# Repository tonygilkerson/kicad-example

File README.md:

# kicad-example

In most cases, my KiCad projects live in a subdirectory named `kicad` within a larger project.

> **Example**: ~/github/tonygilkerson/esphome-projects/garage-door-side-entrance/kicad

This project contains a very simple KiCad project named `hiki` to illiterate how I structure KiCad projects.x

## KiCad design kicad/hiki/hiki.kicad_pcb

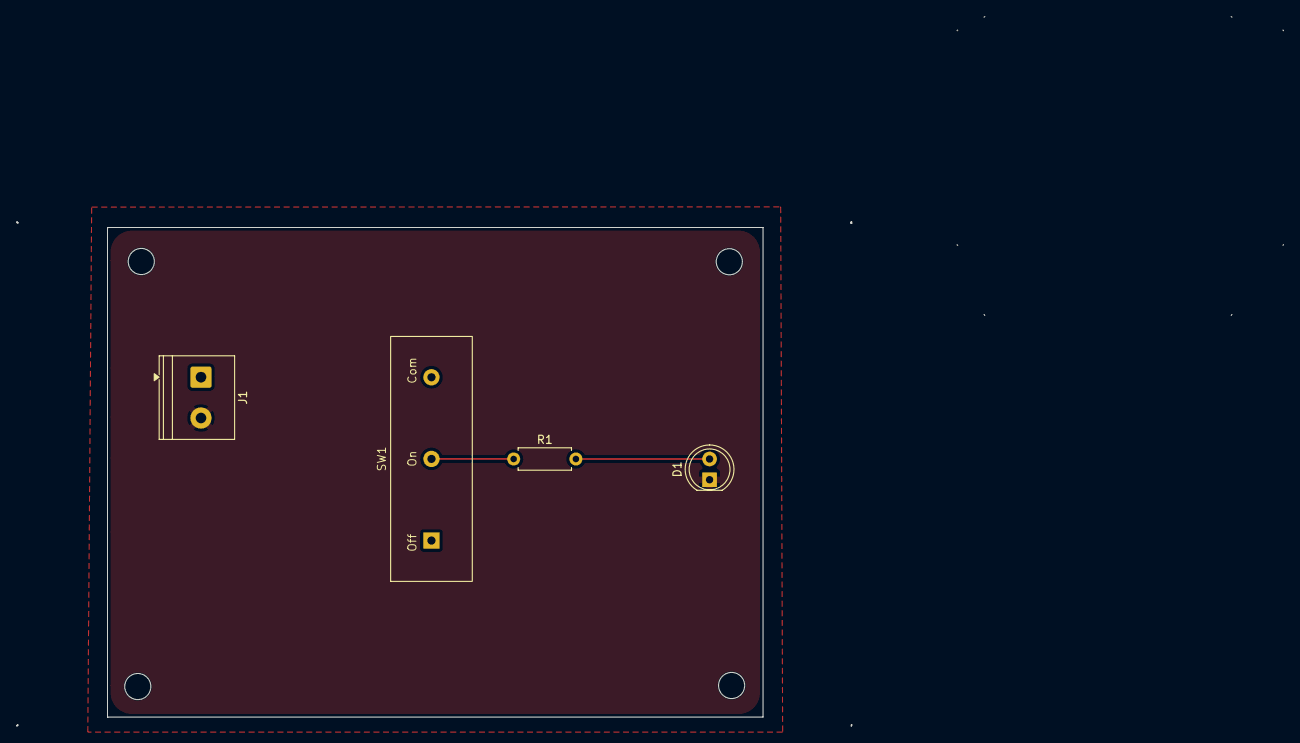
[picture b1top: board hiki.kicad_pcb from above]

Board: 2 copper layers, 80.3 x 60.0 mm, 4 parts (0 on the bottom side), 4 nets.

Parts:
D1: LED; LED_D5.0mm
J1: Screw_Terminal_01x02; TerminalBlock_Phoenix_PT-1,5-2-5.0-H_1x02_P5.00mm_Horizontal
R1: 10m; R_Axial_DIN0207_L6.3mm_D2.5mm_P7.62mm_Horizontal
SW1: SW_SPDT; SWITCH_SPDT_3P

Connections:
GND: D1.1 (K), J1.2
unnamed: D1.2 (A), R1.2
unnamed: R1.1, SW1.2 (on)
VCC: J1.1, SW1.3 (common)

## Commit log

2026-04-15 initial content
2026-04-23 check point
2026-04-23 finish schematic
2026-05-14 save befor adding footprint lib
2026-05-14 add footprint lib and switch footprint
2026-05-15 finish footprint assignments
2026-05-16 done with pcb
